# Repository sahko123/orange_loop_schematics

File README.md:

# Orange Loop Schematics
These schematics were created in

As seen on TV! (probably not but at least its on youtube at https://youtu.be/dBEupkQBFis )

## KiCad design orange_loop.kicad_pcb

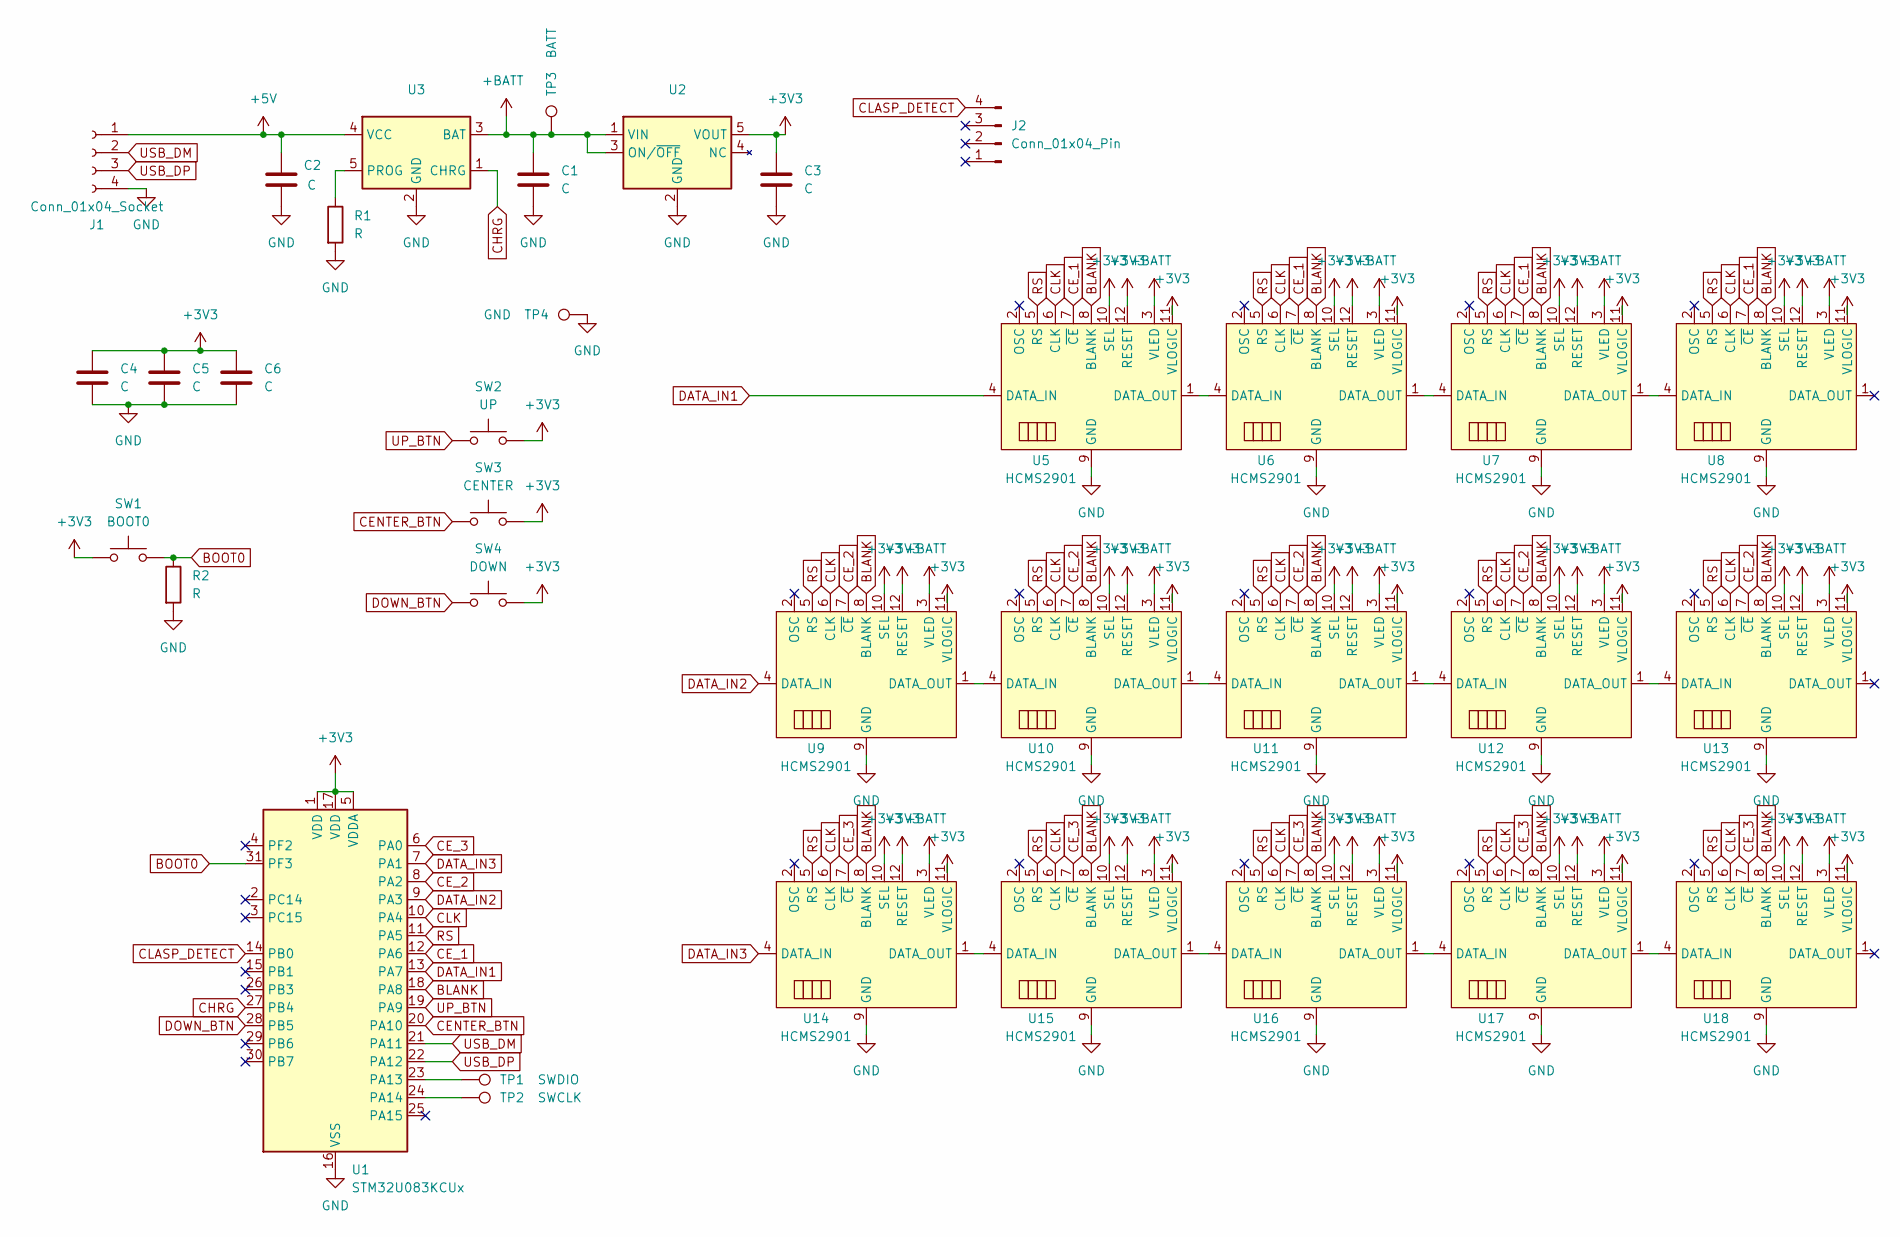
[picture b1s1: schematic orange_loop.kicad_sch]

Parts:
C1, C2, C3, C4, C5, C6: C; C_0402_1005Metric
J1: Conn_01x04_Socket; SMD_2.54_1x04_LONG
J2: Conn_01x04_Pin; SMD_2.54_1x04_SHORT
R1, R2: R; R_0402_1005Metric
SW1: BOOT0; PTS636
SW2: UP; PTS636
SW3: CENTER; PTS636
SW4: DOWN; PTS636
TP1: SWDIO; TestPoint_Pad_D1.5mm
TP2: SWCLK; TestPoint_Pad_D1.5mm
TP3: BATT; TestPoint_Pad_D1.5mm
TP4: GND; TestPoint_Pad_D1.5mm
U1: STM32U083KCUx; QFN-32-1EP_5x5mm_P0.5mm_EP3.45x3.45mm
U2, U3: SOT-23-5
U5, U6, U7, U8, U9, U10, U11, U12, U13, U14, U15, U16, U17, U18: HCMS2901; HCMS2901_SMD

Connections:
+3V3: C3.1, C4.1, C5.1, C6.1, SW1.1, SW2.2, SW3.2, SW4.2, U1.1 (VDD), U1.5 (VDDA), U1.17 (VDD), U2.5 (VOUT), U5.10 (SEL), U5.11 (VLOGIC), U5.12 (RESET), U6.10 (SEL), U6.11 (VLOGIC), U6.12 (RESET), U7.10 (SEL), U7.11 (VLOGIC), U7.12 (RESET), U8.10 (SEL), U8.11 (VLOGIC), U8.12 (RESET), U9.10 (SEL), U9.11 (VLOGIC), U9.12 (RESET), U10.10 (SEL), U10.11 (VLOGIC), U10.12 (RESET), U11.10 (SEL), U11.11 (VLOGIC), U11.12 (RESET), U12.10 (SEL), U12.11 (VLOGIC), U12.12 (RESET), U13.10 (SEL), U13.11 (VLOGIC), U13.12 (RESET), U14.10 (SEL), U14.11 (VLOGIC), U14.12 (RESET), U15.10 (SEL), U15.11 (VLOGIC), U15.12 (RESET), U16.10 (SEL), U16.11 (VLOGIC), U16.12 (RESET), U17.10 (SEL), U17.11 (VLOGIC), U17.12 (RESET), U18.10 (SEL), U18.11 (VLOGIC), U18.12 (RESET)
+5V: C2.1, J1.1, U3.4 (VCC)
+BATT: C1.1, TP3.1, U2.1 (VIN), U2.3 (ON/~OFF), U3.3 (BAT), U5.3 (VLED), U6.3 (VLED), U7.3 (VLED), U8.3 (VLED), U9.3 (VLED), U10.3 (VLED), U11.3 (VLED), U12.3 (VLED), U13.3 (VLED), U14.3 (VLED), U15.3 (VLED), U16.3 (VLED), U17.3 (VLED), U18.3 (VLED)
BLANK: U1.18 (PA8), U5.8 (BLANK), U6.8 (BLANK), U7.8 (BLANK), U8.8 (BLANK), U9.8 (BLANK), U10.8 (BLANK), U11.8 (BLANK), U12.8 (BLANK), U13.8 (BLANK), U14.8 (BLANK), U15.8 (BLANK), U16.8 (BLANK), U17.8 (BLANK), U18.8 (BLANK)
BOOT0: R2.1, SW1.2, U1.31 (PF3)
CENTER_BTN: SW3.1, U1.20 (PA10)
CE_1: U1.12 (PA6), U5.7 (~CE), U6.7 (~CE), U7.7 (~CE), U8.7 (~CE)
CE_2: U1.8 (PA2), U9.7 (~CE), U10.7 (~CE), U11.7 (~CE), U12.7 (~CE), U13.7 (~CE)
CE_3: U1.6 (PA0), U14.7 (~CE), U15.7 (~CE), U16.7 (~CE), U17.7 (~CE), U18.7 (~CE)
CHRG: U1.27 (PB4), U3.1 (CHRG)
CLASP_DETECT: J2.4, U1.14 (PB0)
CLK: U1.10 (PA4), U5.6 (CLK), U6.6 (CLK), U7.6 (CLK), U8.6 (CLK), U9.6 (CLK), U10.6 (CLK), U11.6 (CLK), U12.6 (CLK), U13.6 (CLK), U14.6 (CLK), U15.6 (CLK), U16.6 (CLK), U17.6 (CLK), U18.6 (CLK)
DATA_IN1: U1.13 (PA7), U5.4 (DATA_IN)
DATA_IN2: U1.9 (PA3), U9.4 (DATA_IN)
DATA_IN3: U1.7 (PA1), U14.4 (DATA_IN)
DOWN_BTN: SW4.1, U1.28 (PB5)
GND: C1.2, C2.2, C3.2, C4.2, C5.2, C6.2, J1.4, R1.2, R2.2, TP4.1, U1.16 (VSS), U1.32 (VSS), U1.33 (VSS), U2.2 (GND), U3.2 (GND), U5.9 (GND), U6.9 (GND), U7.9 (GND), U8.9 (GND), U9.9 (GND), U10.9 (GND), U11.9 (GND), U12.9 (GND), U13.9 (GND), U14.9 (GND), U15.9 (GND), U16.9 (GND), U17.9 (GND), U18.9 (GND)
unnamed: TP1.1, U1.23 (PA13)
unnamed: TP2.1, U1.24 (PA14)
unnamed: R1.1, U3.5 (PROG)
unnamed: U5.1 (DATA_OUT), U6.4 (DATA_IN)
unnamed: U6.1 (DATA_OUT), U7.4 (DATA_IN)
unnamed: U7.1 (DATA_OUT), U8.4 (DATA_IN)
unnamed: U9.1 (DATA_OUT), U10.4 (DATA_IN)
unnamed: U10.1 (DATA_OUT), U11.4 (DATA_IN)
unnamed: U11.1 (DATA_OUT), U12.4 (DATA_IN)
unnamed: U12.1 (DATA_OUT), U13.4 (DATA_IN)
unnamed: U14.1 (DATA_OUT), U15.4 (DATA_IN)
unnamed: U15.1 (DATA_OUT), U16.4 (DATA_IN)
unnamed: U16.1 (DATA_OUT), U17.4 (DATA_IN)
unnamed: U17.1 (DATA_OUT), U18.4 (DATA_IN)
RS: U1.11 (PA5), U5.5 (RS), U6.5 (RS), U7.5 (RS), U8.5 (RS), U9.5 (RS), U10.5 (RS), U11.5 (RS), U12.5 (RS), U13.5 (RS), U14.5 (RS), U15.5 (RS), U16.5 (RS), U17.5 (RS), U18.5 (RS)
UP_BTN: SW2.1, U1.19 (PA9)
USB_DM: J1.2, U1.21 (PA11)
USB_DP: J1.3, U1.22 (PA12)

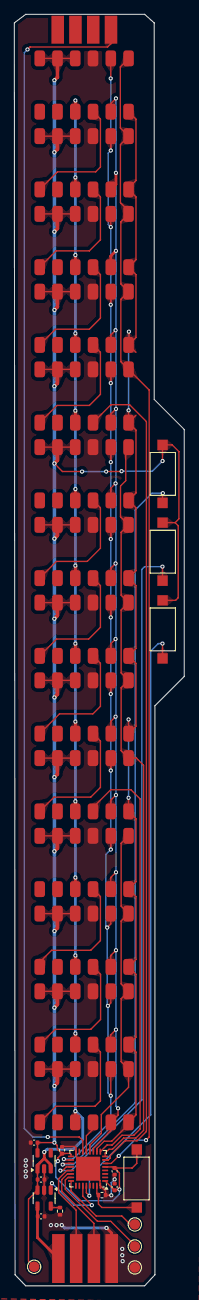
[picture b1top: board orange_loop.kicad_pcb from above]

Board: 2 copper layers, 24.3 x 181.8 mm, 35 parts (0 on the bottom side), 35 nets.

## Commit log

2025-08-05 add schematic and pcb files
